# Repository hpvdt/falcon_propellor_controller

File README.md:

# Propeller Controller

Firmware and hardware design files for the propeller pitch control board, also used to monitor shaft power.

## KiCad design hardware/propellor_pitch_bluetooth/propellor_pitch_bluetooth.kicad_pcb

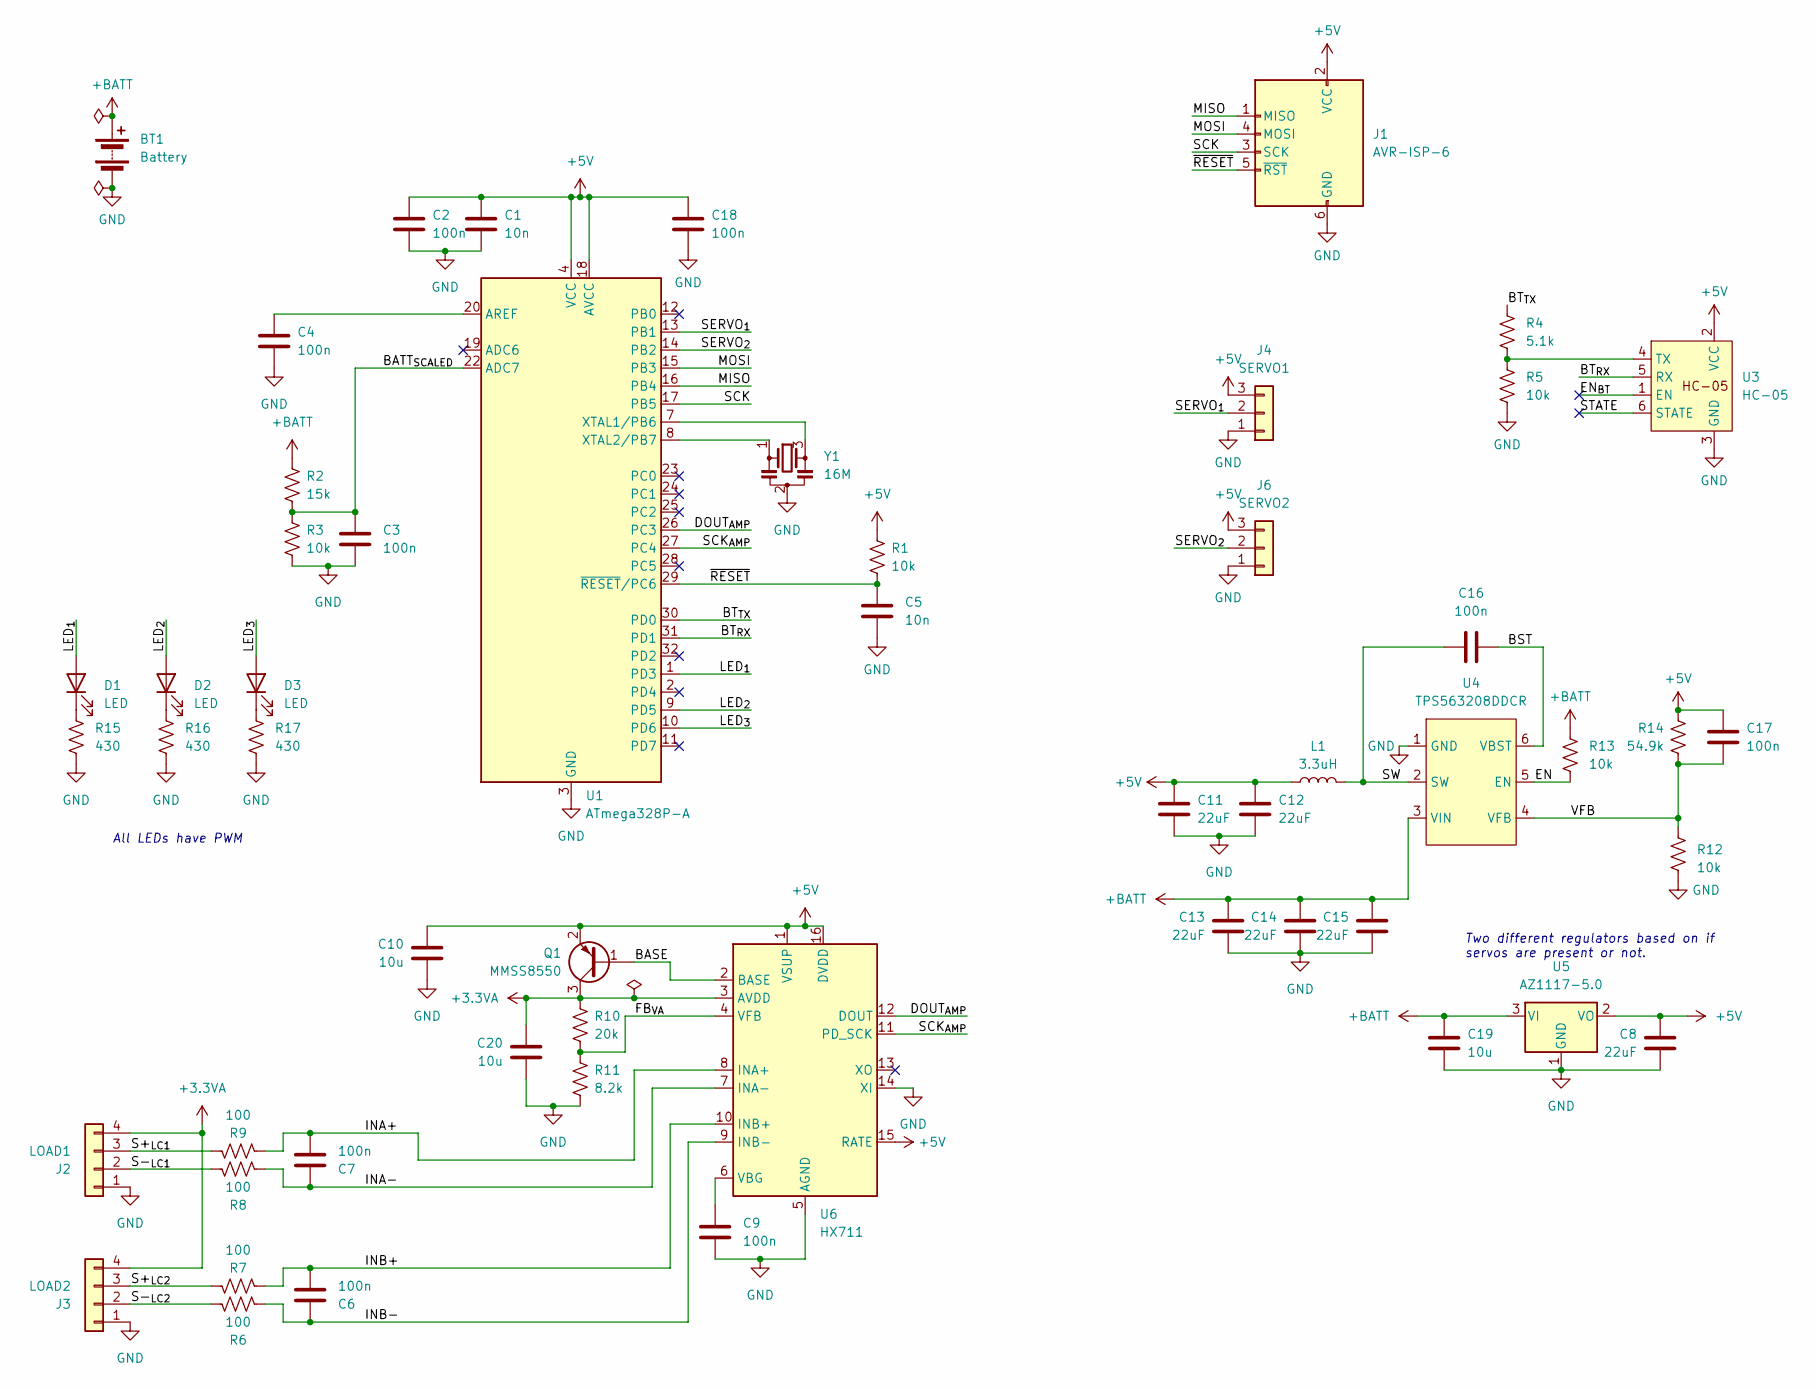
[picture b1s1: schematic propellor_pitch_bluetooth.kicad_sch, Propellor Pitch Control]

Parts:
BT1: Battery; SolderWire-1.5sqmm_1x02_P6mm_D1.7mm_OD3mm_Relief
C1, C5: 10n; C_0603_1608Metric
C2, C3, C4, C6, C7, C9, C18: 100n; C_0603_1608Metric
C8, C11, C12, C13, C14, C15: 22uF; C_0805_2012Metric
C10, C19, C20: 10u; C_0805_2012Metric
C16, C17: 100n; C_0805_2012Metric
D1, D2, D3: LED; LED_0805_2012Metric
J1: AVR-ISP-6; IDC-Header_2x03_P2.54mm_Vertical_SMD
J2: LOAD1; PinHeader_1x04_P2.54mm_Vertical
J3: LOAD2; PinHeader_1x04_P2.54mm_Vertical
J4: SERVO1; JST_EH_B3B-EH-A_1x03_P2.50mm_Vertical
J6: SERVO2; JST_EH_B3B-EH-A_1x03_P2.50mm_Vertical
L1: 3.3uH; L_Taiyo-Yuden_NR-60xx
Q1: MMSS8550; SOT-23
R1, R3, R5, R12, R13: 10k; R_0603_1608Metric
R2: 15k; R_0603_1608Metric
R4: 5.1k; R_0603_1608Metric
R6, R7, R8, R9: 100; R_0603_1608Metric
R10: 20k; R_0603_1608Metric
R11: 8.2k; R_0603_1608Metric
R14: 54.9k; R_0603_1608Metric
R15, R16, R17: 430; R_0603_1608Metric
U1: ATmega328P-A; TQFP-32_7x7mm_P0.8mm
U3: HC-05; PinHeader_1x06_P2.54mm_Vertical
U4: TPS563208DDCR; TSOT-23-6
U5: AZ1117-5.0; SOT-223-3_TabPin2
U6: HX711; SOP-16_3.9x9.9mm_P1.27mm
Y1: 16M; Resonator_SMD_Murata_CSTxExxV-3Pin_3.0x1.1mm

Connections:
+3.3VA: C20.2, J2.4, J3.4, Q1.3 (C), R10.1, U6.3 (AVDD)
+5V: C1.1, C2.1, C8.2, C10.2, C11.2, C12.2, C17.2, C18.1, J1.2 (VCC), J4.3, J6.3, L1.1, Q1.2 (E), R1.1, R14.1, U1.4 (VCC), U1.6 (VCC), U1.18 (AVCC), U3.2 (VCC), U5.2 (VO), U6.1 (VSUP), U6.15 (RATE), U6.16 (DVDD)
+BATT: BT1.1 (+), C13.2, C14.2, C15.2, C19.2, R2.1, R13.2, U4.3 (VIN), U5.3 (VI)
/BASE: Q1.1 (B), U6.2 (BASE)
/BATT_{SCALED}: C3.1, R2.2, R3.1, U1.22 (ADC7)
/BST: C16.2, U4.6 (VBST)
/BT_{RX}: U1.31 (PD1), U3.5 (RX)
/BT_{TX}: R4.1, U1.30 (PD0)
/DOUT_{AMP}: U1.26 (PC3), U6.12 (DOUT)
/EN: R13.1, U4.5 (EN)
/EN_{BT}: U3.1 (EN)
/FB_{VA}: R10.2, R11.1, U6.4 (VFB)
/INA+: C7.2, R9.2, U6.8 (INA+)
/INA-: C7.1, R8.2, U6.7 (INA-)
/INB+: C6.2, R7.2, U6.10 (INB+)
/INB-: C6.1, R6.2, U6.9 (INB-)
/LED_{1}: D1.2 (A), U1.1 (PD3)
/LED_{2}: D2.2 (A), U1.9 (PD5)
/LED_{3}: D3.2 (A), U1.10 (PD6)
/MISO: J1.1 (MISO), U1.16 (PB4)
/MOSI: J1.4 (MOSI), U1.15 (PB3)
/S+_{LC1}: J2.3, R9.1
/S+_{LC2}: J3.3, R7.1
/S-_{LC1}: J2.2, R8.1
/S-_{LC2}: J3.2, R6.1
/SCK: J1.3 (SCK), U1.17 (PB5)
/SCK_{AMP}: U1.27 (PC4), U6.11 (PD_SCK)
/SERVO_{1}: J4.2, U1.13 (PB1)
/SERVO_{2}: J6.2, U1.14 (PB2)
/STATE: U3.6 (STATE)
/SW: C16.1, L1.2, U4.2 (SW)
/VFB: C17.1, R12.2, R14.2, U4.4 (VFB)
/~RESET: C5.1, J1.5 (~RST), R1.2, U1.29 (~RESET/PC6)
GND: BT1.2 (-), C1.2, C2.2, C3.2, C4.2, C5.2, C8.1, C9.1, C10.1, C11.1, C12.1, C13.1, C14.1, C15.1, C18.2, C19.1, C20.1, J1.6 (GND), J2.1, J3.1, J4.1, J6.1, R3.2, R5.2, R11.2, R12.1, R15.2, R16.2, R17.2, U1.3 (GND), U1.5 (GND), U1.21 (GND), U3.3 (GND), U4.1 (GND), U5.1 (GND), U6.5 (AGND), U6.14 (XI), Y1.2
unnamed: D1.1 (K), R15.1
unnamed: D2.1 (K), R16.1
unnamed: D3.1 (K), R17.1
unnamed: C4.1, U1.20 (AREF)
unnamed: U1.7 (XTAL1/PB6), Y1.3
unnamed: U1.8 (XTAL2/PB7), Y1.1
unnamed: R4.2, R5.1, U3.4 (TX)
unnamed: C9.2, U6.6 (VBG)

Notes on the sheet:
All LEDs have PWM
Two different regulators based on if servos are present or not.

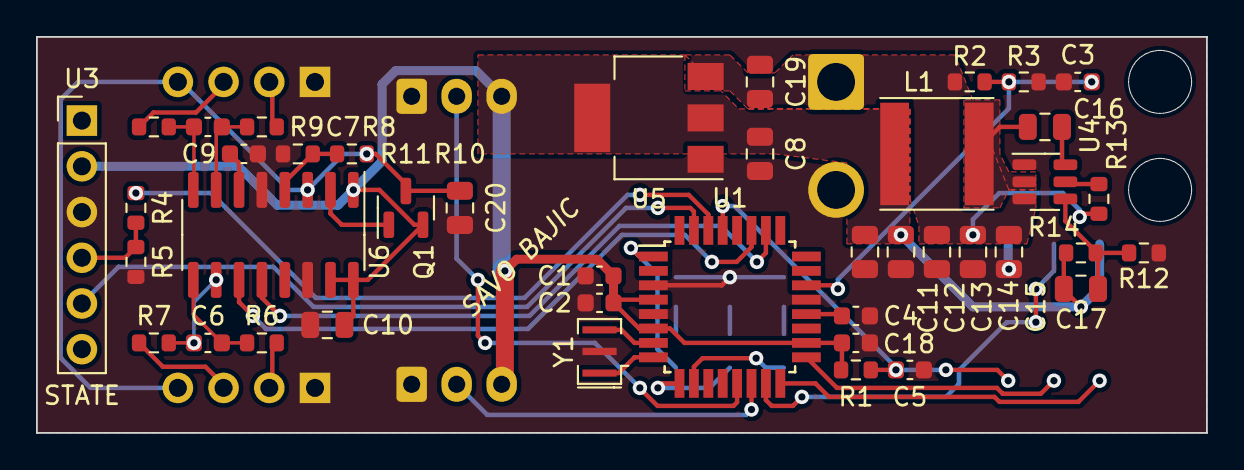
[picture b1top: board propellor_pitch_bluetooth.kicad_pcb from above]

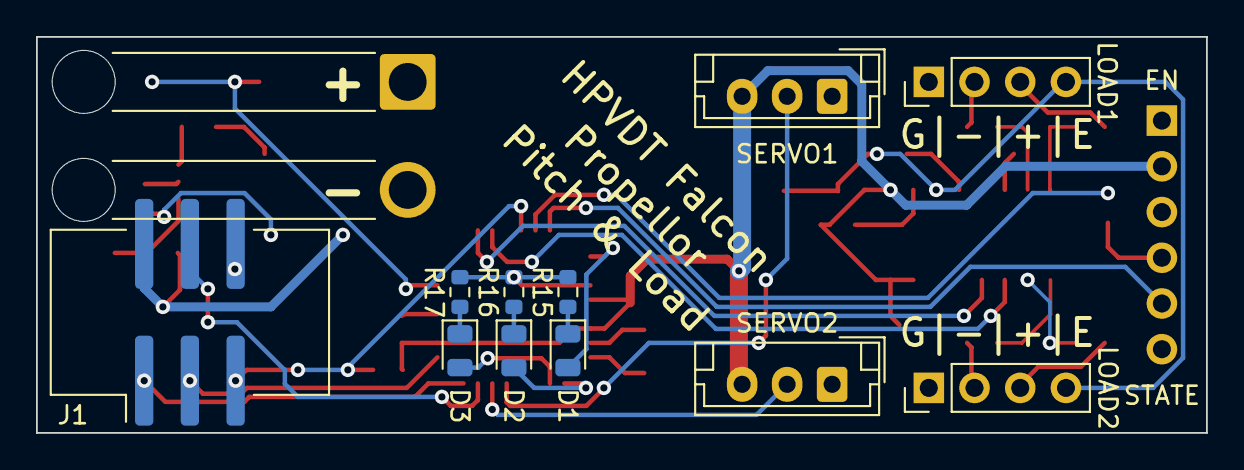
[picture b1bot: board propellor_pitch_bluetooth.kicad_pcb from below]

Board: 2 copper layers, 65.0 x 22.0 mm, 54 parts (12 on the bottom side), 40 nets.

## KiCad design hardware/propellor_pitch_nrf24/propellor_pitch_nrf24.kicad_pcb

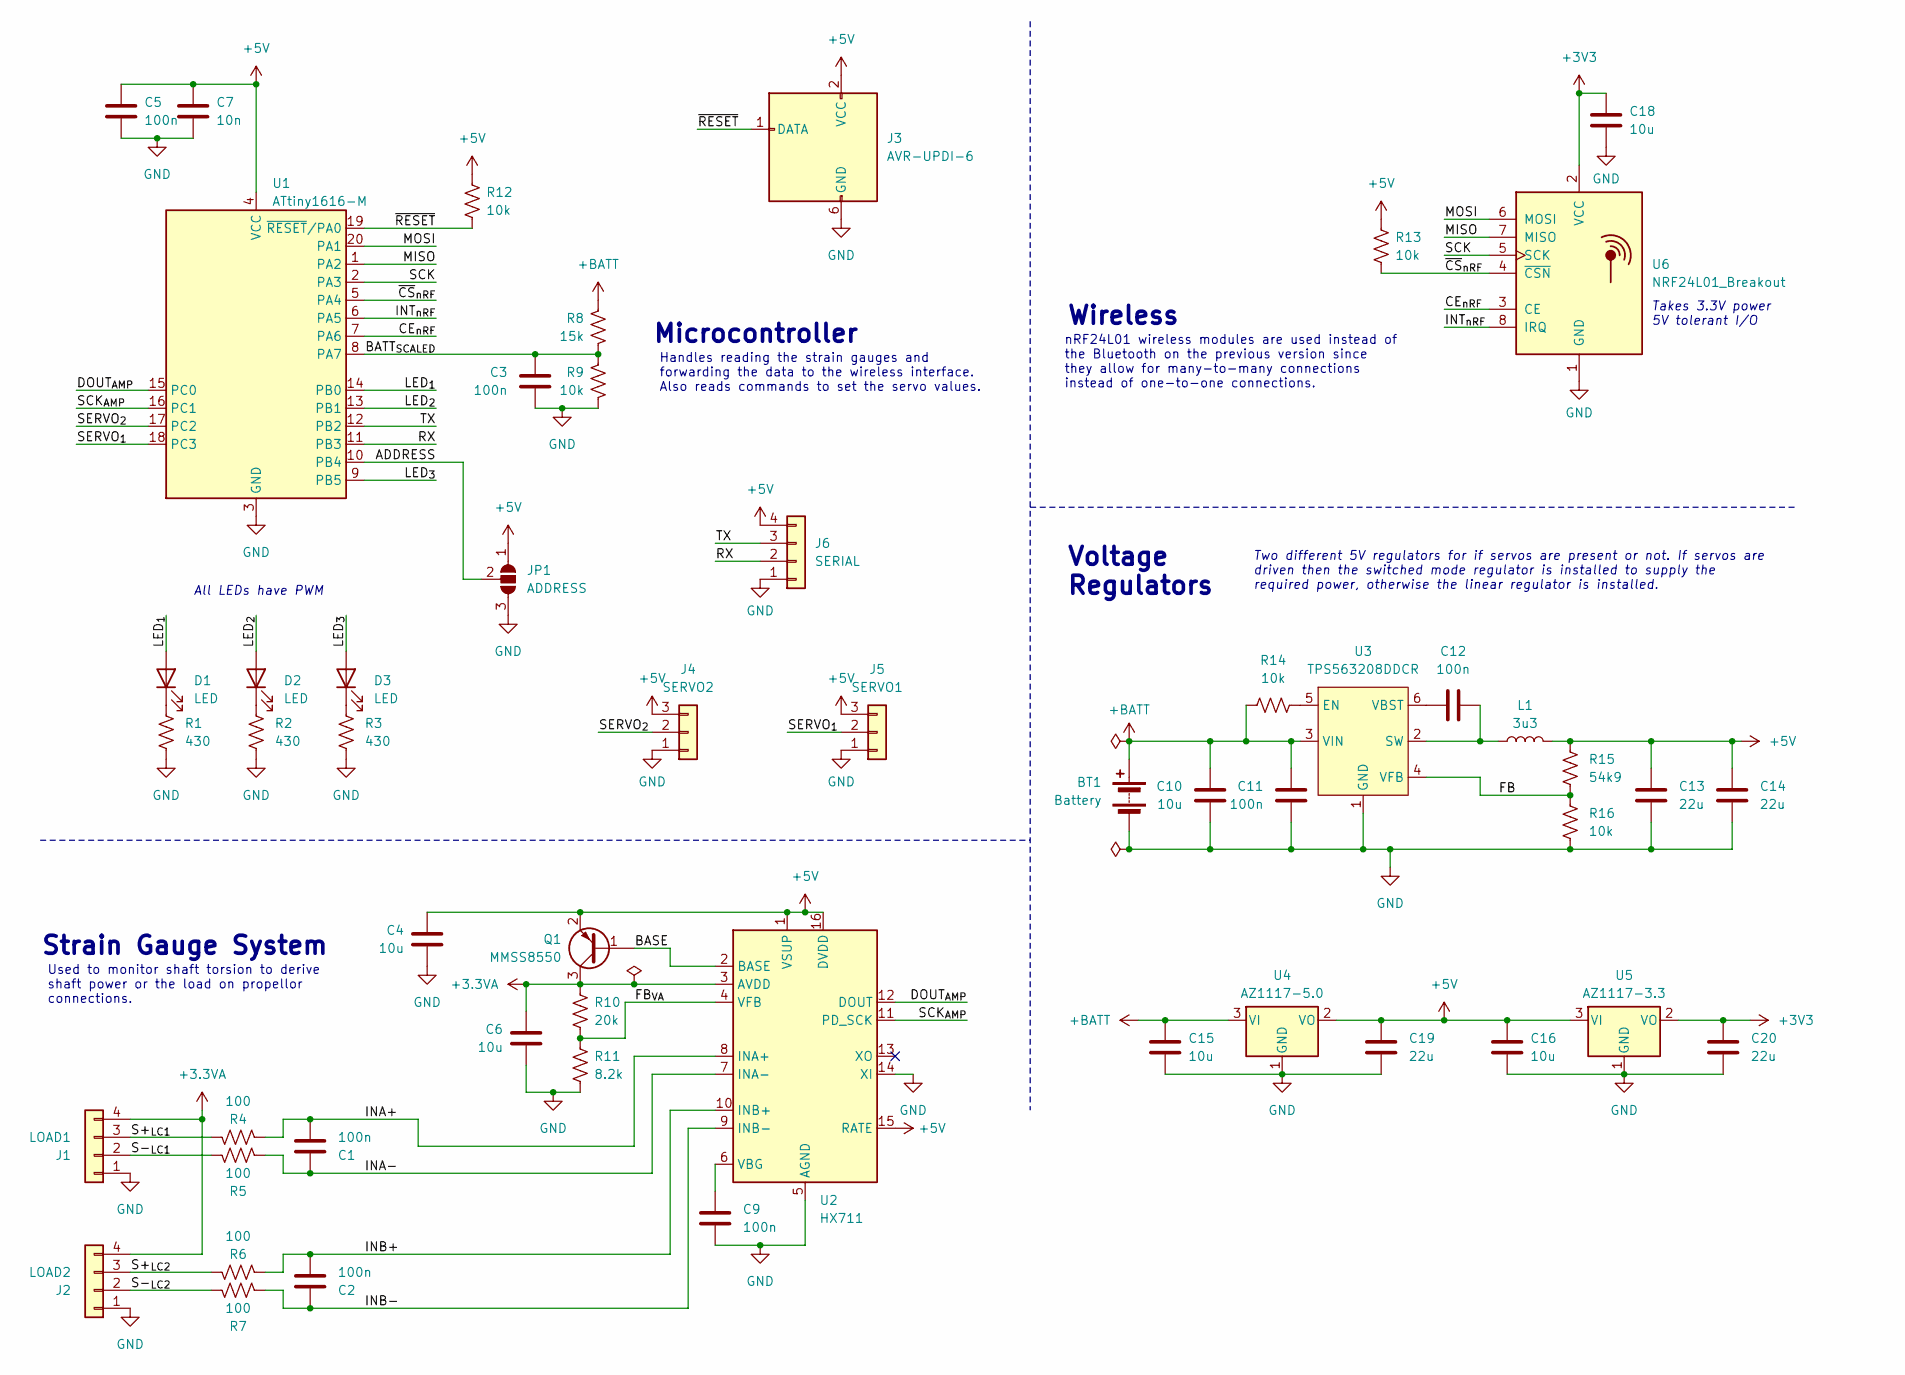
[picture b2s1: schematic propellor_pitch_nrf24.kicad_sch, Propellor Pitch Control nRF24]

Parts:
BT1: Battery; SolderWire-1.5sqmm_1x02_P6mm_D1.7mm_OD3mm_Relief
C1, C2, C3, C5, C9, C11: 100n; C_0603_1608Metric
C4, C6, C10, C15, C16, C18: 10u; C_0805_2012Metric
C7: 10n; C_0603_1608Metric
C12: 100n; C_0805_2012Metric
C13, C14, C19, C20: 22u; C_0805_2012Metric
D1, D2, D3: LED; LED_0805_2012Metric
J1: LOAD1; PinHeader_1x04_P2.54mm_Vertical
J2: LOAD2; PinHeader_1x04_P2.54mm_Vertical
J3: AVR-UPDI-6; PinHeader_2x03_P2.54mm_Vertical_SMD
J4: SERVO2; JST_EH_B3B-EH-A_1x03_P2.50mm_Vertical
J5: SERVO1; JST_EH_B3B-EH-A_1x03_P2.50mm_Vertical
J6: SERIAL; PinHeader_1x04_P2.54mm_Vertical
JP1: ADDRESS; SolderJumper-3_P1.3mm_Open_Pad1.0x1.5mm
L1: 3u3; L_Taiyo-Yuden_NR-60xx
Q1: MMSS8550; SOT-23
R1, R2, R3: 430; R_0603_1608Metric
R4, R5, R6, R7: 100; R_0603_1608Metric
R8: 15k; R_0603_1608Metric
R9, R12, R13, R14, R16: 10k; R_0603_1608Metric
R10: 20k; R_0603_1608Metric
R11: 8.2k; R_0603_1608Metric
R15: 54k9; R_0603_1608Metric
U1: ATtiny1616-M; VQFN-20-1EP_3x3mm_P0.4mm_EP1.7x1.7mm
U2: HX711; SOP-16_3.9x9.9mm_P1.27mm
U3: TPS563208DDCR; TSOT-23-6
U4: AZ1117-5.0; SOT-223-3_TabPin2
U5: AZ1117-3.3; SOT-223-3_TabPin2
U6: NRF24L01_Breakout; nRF24L01_Breakout

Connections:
+3.3VA: C6.2, J1.4, J2.4, Q1.3 (C), R10.1, U2.3 (AVDD)
+3V3: C18.2, C20.2, U5.2 (VO), U6.2 (VCC)
+5V: C4.2, C5.1, C7.1, C13.2, C14.2, C16.2, C19.2, J3.2 (VCC), J4.3, J5.3, J6.4, JP1.1 (A), L1.2, Q1.2 (E), R12.1, R13.1, R15.1, U1.4 (VCC), U2.1 (VSUP), U2.15 (RATE), U2.16 (DVDD), U4.2 (VO), U5.3 (VI)
+BATT: BT1.1 (+), C10.2, C11.2, C15.2, R8.1, R14.1, U3.3 (VIN), U4.3 (VI)
/ADDRESS: JP1.2 (C), U1.10 (PB4)
/BASE: Q1.1 (B), U2.2 (BASE)
/BATT_{SCALED}: C3.1, R8.2, R9.1, U1.8 (PA7)
/CE_{nRF}: U1.7 (PA6), U6.3 (CE)
/DOUT_{AMP}: U1.15 (PC0), U2.12 (DOUT)
/FB: R15.2, R16.2, U3.4 (VFB)
/FB_{VA}: R10.2, R11.1, U2.4 (VFB)
/INA+: C1.2, R4.2, U2.8 (INA+)
/INA-: C1.1, R5.2, U2.7 (INA-)
/INB+: C2.2, R6.2, U2.10 (INB+)
/INB-: C2.1, R7.2, U2.9 (INB-)
/INT_{nRF}: U1.6 (PA5), U6.8 (IRQ)
/LED_{1}: D1.2 (A), U1.14 (PB0)
/LED_{2}: D2.2 (A), U1.13 (PB1)
/LED_{3}: D3.2 (A), U1.9 (PB5)
/MISO: U1.1 (PA2), U6.7 (MISO)
/MOSI: U1.20 (PA1), U6.6 (MOSI)
/RX: J6.2, U1.11 (PB3)
/S+_{LC1}: J1.3, R4.1
/S+_{LC2}: J2.3, R6.1
/S-_{LC1}: J1.2, R5.1
/S-_{LC2}: J2.2, R7.1
/SCK: U1.2 (PA3), U6.5 (SCK)
/SCK_{AMP}: U1.16 (PC1), U2.11 (PD_SCK)
/SERVO_{1}: J5.2, U1.18 (PC3)
/SERVO_{2}: J4.2, U1.17 (PC2)
/TX: J6.3, U1.12 (PB2)
/~CS_{nRF}: R13.2, U1.5 (PA4), U6.4 (~CSN)
/~RESET: J3.1 (DATA), R12.2, U1.19 (~RESET/PA0)
GND: BT1.2 (-), C3.2, C4.1, C5.2, C6.1, C7.2, C9.1, C10.1, C11.1, C13.1, C14.1, C15.1, C16.1, C18.1, C19.1, C20.1, J1.1, J2.1, J3.6 (GND), J4.1, J5.1, J6.1, JP1.3 (B), R1.2, R2.2, R3.2, R9.2, R11.2, R16.1, U1.3 (GND), U1.21 (GND), U2.5 (AGND), U2.14 (XI), U3.1 (GND), U4.1 (GND), U5.1 (GND), U6.1 (GND)
unnamed: D1.1 (K), R1.1
unnamed: D2.1 (K), R2.1
unnamed: D3.1 (K), R3.1
unnamed: C9.2, U2.6 (VBG)
unnamed: R14.2, U3.5 (EN)
unnamed: C12.2, L1.1, U3.2 (SW)
unnamed: C12.1, U3.6 (VBST)

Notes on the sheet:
Wireless
Voltage Regulators
Microcontroller
Strain Gauge System
Takes 3.3V power 5V tolerant I/O
All LEDs have PWM
nRF24L01 wireless modules are used instead of the Bluetooth on the previous version since they allow for many-to-many connections instead of one-to-one connections.
Handles reading the strain gauges and forwarding the data to the wireless interface. Also reads commands to set the servo values.
Two different 5V regulators for if servos are present or not. If servos are driven then the switched mode regulator is installed to supply the required power, otherwise the linear regulator is installed.
Used to monitor shaft torsion to derive shaft power or the load on propellor connections.

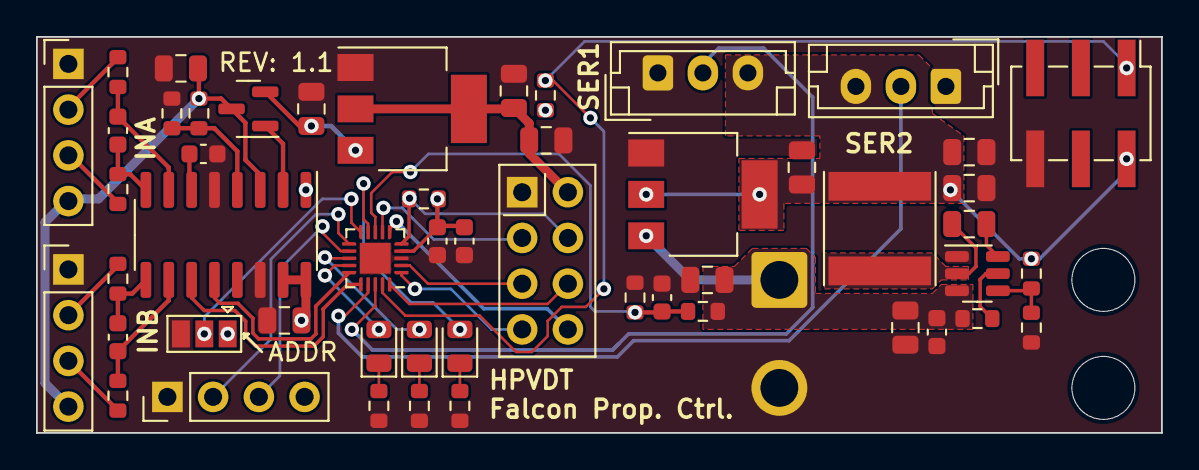
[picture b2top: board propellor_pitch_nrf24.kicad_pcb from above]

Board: 2 copper layers, 62.5 x 22.0 mm, 53 parts (1 on the bottom side), 41 nets.

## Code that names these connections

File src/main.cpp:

#include <Arduino.h>

//HX711
#include <HX711.h>

//RF24
#include <RF24.h>
#include <SPI.h>

// Let these addresses be used for the pair
uint8_t address[][6] = { "1Node", "2Node" };
// It is very helpful to think of an address as a path instead of as
// an identifying device destination

// to use different addresses on a pair of radios, we need a variable to
// uniquely identify which address this radio will use to transmit
bool radioNumber = 0;  // 0 uses address[0] to transmit, 1 uses address[1] to transmit

// For this example, we'll be using a payload containing
// a single float number that will be incremented
// on every successful transmission
float receivedFloat = 0.0;

// Instantiate an object for the nRF24L01 transceiver
const pin_size_t CE_PIN = PIN_PA6;
const pin_size_t CSN_PIN = PIN_PA4;
const pin_size_t MOSI_PIN = PIN_PA1;
const pin_size_t MISO_PIN = PIN_PA2;
const pin_size_t CLOCK = PIN_PA3;
RF24 radio(CE_PIN, CSN_PIN);

// Make a data structure to store the entire payload of different datatypes
struct PayloadStruct {
  long readings[2];
};
PayloadStruct response;

// HX711 circuit wiring
const pin_size_t LOADCELL_DOUT_PIN = PIN_PC0;
const pin_size_t LOADCELL_SCK_PIN = PIN_PC1;
const pin_size_t GAUGE_TIMEOUT = 10; // Timeout in ms for waiting for strain gauge data

long channel_A;
long channel_B;

HX711 scale;

//Servo
#include <Servo.h>

Servo servo1;
Servo servo2;
const pin_size_t SERVO1_PIN = PIN_PC2;
const pin_size_t SERVO2_PIN = PIN_PC3;

// LED pins
const pin_size_t pinLED1 = PIN_PB0;
const pin_size_t pinLED2 = PIN_PB1;
const pin_size_t pinLED3 = PIN_PB5;

// Table lookup
const float CONTROL_ANGLES[]      = { 0.0, 1.0, 2.0, 3.0, 4.0, 5.0, 6.0, 7.0, 8.0, 9.0};
const unsigned int SERVO_ANGLES[] = {  15,  17,  19,  21,  23,  25,  27,  29,  31,  33};
const int NUMBER_OF_ANGLES = sizeof(CONTROL_ANGLES) / sizeof(CONTROL_ANGLES[0]);

unsigned int getServoAngle(float desiredControlAngle) {
  // Ensure it's valid and clamped
  if (isnan(desiredControlAngle)) desiredControlAngle = 0;
  if (desiredControlAngle <= CONTROL_ANGLES[0]) return SERVO_ANGLES[0];
  if (desiredControlAngle >= CONTROL_ANGLES[NUMBER_OF_ANGLES - 1]) return SERVO_ANGLES[NUMBER_OF_ANGLES - 1];

  unsigned int interpolated = 90; // Value to interpolate from lookup table, defaults to mid-range
  
  // Interpolate
  for (int i = 1; i < (NUMBER_OF_ANGLES - 1); i++) {
    if (CONTROL_ANGLES[i] > desiredControlAngle) {
      // Interpolate in this bracket
      const float dx = CONTROL_ANGLES[i] - CONTROL_ANGLES[i - 1];
      const float dy = SERVO_ANGLES[i] - SERVO_ANGLES[i - 1];
      const float portion = (desiredControlAngle - CONTROL_ANGLES[i - 1]) / dx;

      interpolated = SERVO_ANGLES[i - 1] + (dy * portion);
      break;
    }
  }

  return interpolated;
}

void setup() {

  //UART and HX711
  Serial.begin(9600);
  delay(1000);

  scale.begin(LOADCELL_DOUT_PIN, LOADCELL_SCK_PIN);

  //LED tests
  pinMode(pinLED1, OUTPUT);
  pinMode(pinLED2, OUTPUT);
  pinMode(pinLED3, OUTPUT);

  //Do you like flashing LEDs? Then UNCOMMENT THIS LED TEST!
  digitalWrite(pinLED1, HIGH);
  delay(20);
  digitalWrite(pinLED2, HIGH);
  delay(20);
  digitalWrite(pinLED3, HIGH);
  delay(20);
  digitalWrite(pinLED1, LOW);
  delay(20);
  digitalWrite(pinLED2, LOW);
  delay(20);
  digitalWrite(pinLED3, LOW);
  delay(20);

  //Servo
  servo1.attach(SERVO1_PIN); 
  servo2.attach(SERVO2_PIN); 

  // RF 24

  if (!radio.begin()) {
    Serial.println(F("radio hardware is not responding!!"));
    while (1) {}  // hold in infinite loop
  }
  else Serial.println("Radio okay");


  radio.setPALevel(RF24_PA_HIGH);  // RF24_PA_MAX is default.

  // to use ACK payloads, we need to enable dynamic payload lengths (for all nodes)
  radio.enableDynamicPayloads();  // ACK payloads are dynamically sized

  // Acknowledgement packets have no payloads by default. We need to enable
  // this feature for all nodes (TX & RX) to use ACK payloads.
  radio.enableAckPayload();

  // set the TX address of the RX node into the TX pipe
  radio.openWritingPipe(address[radioNumber]);  // always uses pipe 0

  radio.openReadingPipe(1, address[!radioNumber]);  // using pipe 1
  radio.startListening();  // put radio in RX mode

  radio.writeAckPayload(1, &response, sizeof(response)); // Initial dummy response to serve

  digitalWrite(pinLED1, HIGH);
}

void loop() {

  // UART and HX711

  scale.set_gain(32); // Set HX711 to read channel B after this read
  Serial.println("Channel A");
  if (scale.wait_ready_timeout(GAUGE_TIMEOUT)) {
    channel_A = scale.read();
    Serial.print("HX711 reading Channel A: ");
    Serial.println(channel_A);
  } else {
    Serial.println("HX711 Channel A not found.");
  }
  // Read on Channel B
  scale.set_gain(128); // Set HX711 to read channel A after this read
  if (scale.wait_ready_timeout(GAUGE_TIMEOUT)) {
    channel_B = scale.read();
    Serial.print("HX711 reading Channel B: ");
    Serial.println(channel_B);
  } else {
    Serial.println("HX711 Channel B not found.");
  }

  // This device is a RX node
  // Set ack payload response to channel A and channel B readings
 
  response.readings[0] = channel_A;
  response.readings[1] = channel_B;

  uint8_t pipe;
  if (radio.available(&pipe)) {              // is there a payload? get the pipe number that recieved it
    uint8_t bytes = radio.getPayloadSize();  // get the size of the payload
    radio.read(&receivedFloat, bytes);             // fetch payload from FIFO
    Serial.println(receivedFloat);  // print the payload's value

    Serial.println(response.readings[0]);    // print outgoing message
    // load the payload for the first received transmission on pipe 0
    radio.writeAckPayload(1, &response, sizeof(response));

    // Update servos with newest angle
    unsigned int angle = getServoAngle(receivedFloat);
    servo1.write(angle);
    servo2.write(angle);
  }
}

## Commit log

2023-09-23 Initialization of PlatformIO project
2024-02-02 Ignore `DS_Store`
2024-02-02 Flashing_Lights
2024-02-02 Your mom
2024-02-10 Servo1 and servo2 connections test (successful)
2024-02-23 Savo is Cool - George Addition of HX711 test from library example and readings
2024-02-28 Change from channel A to channel B: to test
2024-03-13 03/12 Changes RF24
2024-03-22 Added RF24 Code from GettingStarted
2024-03-22 RF24 Transmitting
2024-03-27 Added Recieve
2024-03-30 Ack payloads with channel A and channel B readings
2024-04-10 Added interpolation setup code
2024-04-10 Fixed Changes
2024-05-16 Minor touch ups
    - Fixed indentation
    - Set the gain settings to be set correctly to align with the reads for a given channel
    - Re-ordered and cleaned up `setup()`
2024-05-16 Removed servo sweeping code
2024-05-16 Added gauge timeout constant
2024-05-16 Added interpolation for servo angles
2024-08-10 Tidied up pin allocations
2025-08-17 Reorganized repo to add hardware designs
